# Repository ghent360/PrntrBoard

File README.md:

Prntr Board V1
======================
## *Deprecated*
**This project has run it's course. Most of the features are complete and there is little I can improve further. I have switched my focus to the [V2 design](https://github.com/ghent360/PrntrBoardV2).**

------------------

PrntrBoard is a 3D printer controller board designed to work with STM32 NUCLEO dev kits. The current version (V1) supports NUCLEO-64 series kits. The design is being developed on F446-RE kit, but other models could work as well. IMO the STM32F446 NUCLEO-64 kit offers very good performance (180MHz CPU) for the price ($15).

Some features of the board:
-----
  + 5x Trinamic super quiet drivers (TMC2130, TMC2660 or TMC2209)
  + Marlin 2.0 firmware
  + (2+2) controllable fans and 2x "always on" fan connectors
  + 3x min and max endstops for the x, y and z axis
  + 2x end stops for fillament end detection
  + SPI or I2C display connector for ST7735 or SSD1306 screen + one button and rotary encoder
  + Dual thermocouple connectors (for MAX31866, MAX31855 or MAX6675 boards)
  + Input voltage (Vin): 12-24V
  + selectable fan voltage (5V or Vin)

Because the NUCLEO-64 has limited number of IO pins, some compromises had to be made:
  + ~~No sd-card~~ (sd-card is added using new NUCLEO-64 compatible board)
  + The thermocouple connectors share pins with the E0 and E1 cool fan controls. You'll have to decide to use one or the other via jumpers on the board. Most printers I've seen come with "always on" extruder fans, the choice seemed like a worthy sacrifice.

Generic shortcuts I don't plan to improve:
------
  + ~~5V power supply is external. These are available from various resellers and fairly cheap - less than $1. No need to waste board layout space and component count.~~ (this has beed addresses with the new NUCLEO-64 compatible daugherboard)
  + Heated bed MOSFET - large heated beds consume a lot of power and it is challenging to provision the design for > 20A current (there is simply not enough copper space on the board to support this current). External heated bed MOSFETs are very affordable < $10 and support 20A-40A with no issues. If you have large heated bed - use external MOSFET or SSR.

Details
------
I use the daily build of KiCad (soon to be released V6) - let me know if you have trouble opening the files.

The current PCB desing is using 4 layer board, 6/6 mil track width/clearance, 12 mil min via hole size and 20 mil via diameter.

There are tree active branches:
  + tmc2130 - the board design for TMC2130 drivers
  + tmc2130-redesign - redesign of the TMC2130 branch with the nucleo board flipped
  + tmc2660 - the board design for TMC2660 drivers
  + tmc2209 - the board design for TMC2209 drivers

TMC2130 and TMC2660 PCB designs use the QFP version of the driver ICs, because they can handle a bit more power. The TMC2209 is available only in QFN package.

Status
------
TMC2130 version is table and been running for over a year. TMC2660 is being tested at the moment. Prototypes of the TMC2209 are being made.

old status:
I've been running a prototype of this board for a few months now and I'm very happy with the board stability. I'm trying to figure out how to make these at scale.

I have made prototypes of the TMC2130 board design (rev0) - the board has a few bugs, that are corrected in the rev1 version. Rev0 did not have LCD screen, it was added in Rev1. I'm trying to work-out the thermal design issues.
Rev1 board have been ordered and the dev branch is now switched to Rev2. The thermocouple connectors are added Rev2.
Rev2 borads have been ordered. The current working board is rev3. Added 2 more pins to the LCD connector
for the rotary encoder input. I also re-connected the E1 and E0 CS pins, so the LCD pins can be connected
to the hardware I2C pins. This way one can use SPI or I2C screens.

This branch is a redesign of the TMC2130 board. The main difference is that the NUCLEO board is flipped in a more natural position. In addition I'm now using a dedicated ground plane, larger heatsink areas for the mosfets. I'm much happier with the thermal layout of this branch.

The NUCLEO-64 board was limiting the design in many ways. I have a replacement board using STM32F407VE. This is 100 pin part. The new daughter board is the same form factor as the NUCLEO-64. It adds SPI EEPROM as well as native USB interface and micro SD-Card socket. The new board also has enough space for 24V to 5V buck converter, so power supply can beintegrated.

Tested circuits:
  + Heater control
  + Thermistor input
  + Fan control
  + Motor driver control
  + Z probe
  + End stops
  + Thermocuple interface (tested MAX31855 with Smoothieware)
  + LCD interface (tested REPRAP discount full graphics controller - the panel has issues
  sharing the SPI port with the TMC drivers. Could be solved with adapter board with extra AND gate)

Circuits that need verification:
  + Stall guard alert from the motor driver

Software
------

The software for the board is a clone of Marlin at [bugfix-2.0.x branch](https://github.com/ghent360/Marlin/tree/bugfix-2.0.x/ "Github.com") of my repository. It is quite usable. I keep it relatively in sync with the Marlin branch. *Note: there are other branches of Marlin, only the bugfix-2.0.x supports the STM32 microcontroller.*

Marlin is using Adruino IDE or Platform IO. I personally had issues with Platform IO not supporting the STM32F4 board, so I use Arduino version 1.8.5. To compile the firmware code you would need to install the [STM32 Arduino port](https://github.com/stm32duino/Arduino_Core_STM32 "www.stm32duino.com").

I'm also porting [Smoothieware](http://smoothieware.org) V1 to the board. So far I got the heater control and the stepper drivers working. My smoothie port is available [here](https://github.com/ghent360/Smoothieware-STM32F4 "Gitgub.com"). Please not the Smoothie port is not ready yet (there is an issue with the ADC). I have done only minimal tests so far.

Visit [my blog](https://blog.pcbxprt.com/) for status updates on the development of the board.

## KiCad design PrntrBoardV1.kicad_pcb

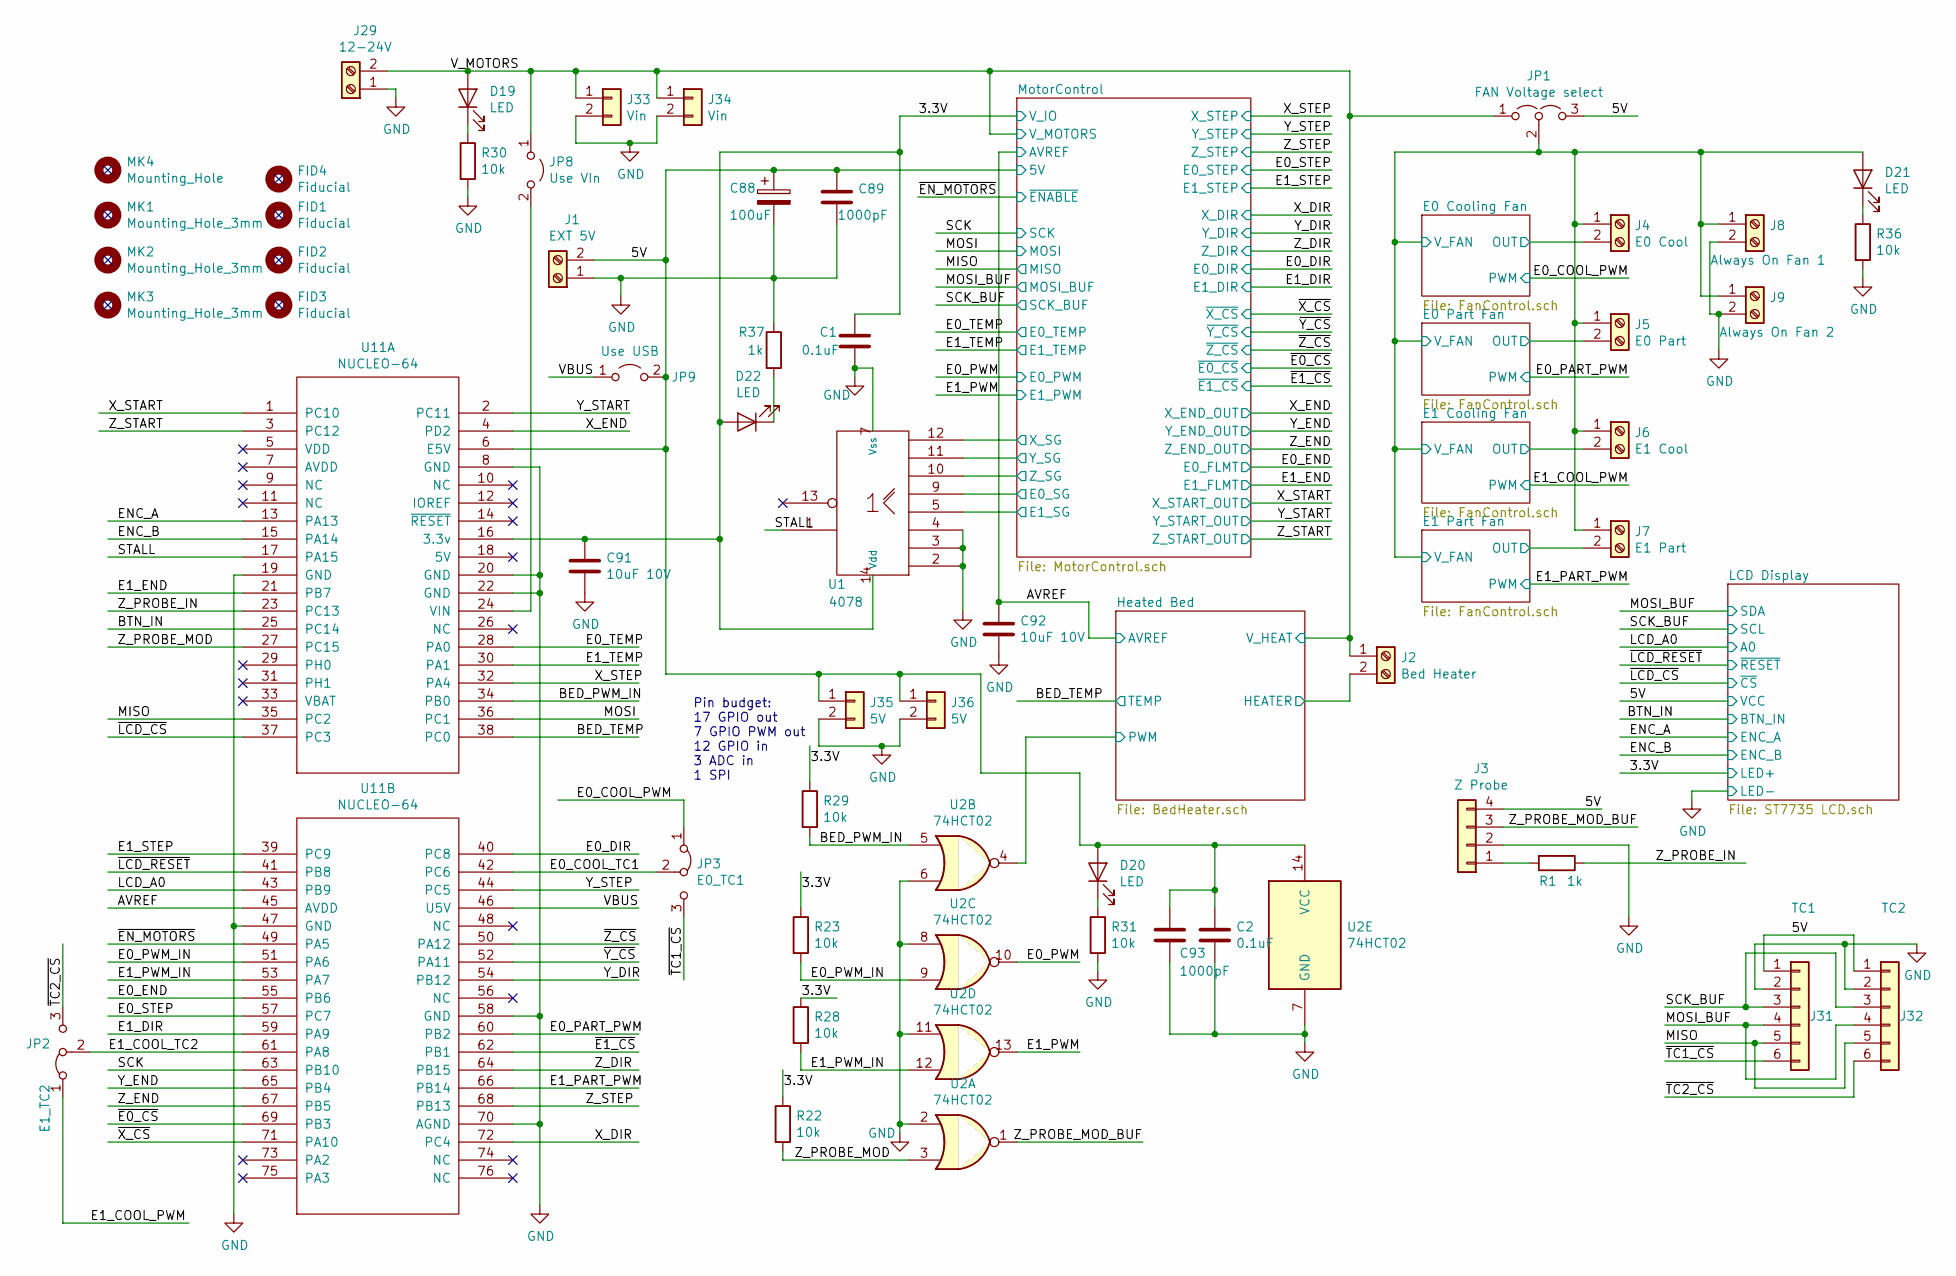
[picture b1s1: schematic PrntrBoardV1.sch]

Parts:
C1, C2: 0.1uF; C_0603_1608Metric
C88: 100uF; CP_Elec_6.3x7.7
C89, C93: 1000pF; C_0603_1608Metric
C91, C92: 10uF 10V; C_0603_1608Metric
D19, D20, D21, D22: LED; LED_0603_1608Metric
FID1, FID2, FID3, FID4: Fiducial; Fiducial_1mm_Dia_2.54mm_Outer_CopperTop
J1: EXT 5V; TerminalBlock_Phoenix_PT-1,5-2-3.5-H_1x02_P3.50mm_Horizontal
J2: Bed Heater; TerminalBlock_Phoenix_MKDS-1,5-2-5.08_1x02_P5.08mm_Horizont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
J3: Z Probe; PinHeader_1x04_P2.54mm_Vertical
J4: E0 Cool; TerminalBlock_Phoenix_PT-1,5-2-3.5-H_1x02_P3.50mm_Horizontal
J5: E0 Part; TerminalBlock_Phoenix_PT-1,5-2-3.5-H_1x02_P3.50mm_Horizontal
J6: E1 Cool; TerminalBlock_Phoenix_PT-1,5-2-3.5-H_1x02_P3.50mm_Horizontal
J7: E1 Part; TerminalBlock_Phoenix_PT-1,5-2-3.5-H_1x02_P3.50mm_Horizontal
J8: Always On Fan 1; TerminalBlock_Phoenix_PT-1,5-2-3.5-H_1x02_P3.50mm_Horizontal
J9: Always On Fan 2; TerminalBlock_Phoenix_PT-1,5-2-3.5-H_1x02_P3.50mm_Horizontal
J29: 12-24V; TerminalBlock_MetzConnect_Type701_RT11L02HGLU_1x02_P6.35mm_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
J31: TC1; PinHeader_1x06_P2.54mm_Vertical
J32: TC2; PinHeader_1x06_P2.54mm_Vertical
J33, J34: Vin; PinHeader_1x02_P2.54mm_Vertical
J35, J36: 5V; PinHeader_1x02_P2.54mm_Vertical
JP1: FAN Voltage select; PinHeader_1x03_P2.54mm_Vertical
JP2: E1_TC2; PinHeader_1x03_P2.54mm_Vertical
JP3: E0_TC1; PinHeader_1x03_P2.54mm_Vertical
JP8: Use VIn; PinHeader_1x02_P2.54mm_Vertical
JP9: Use USB; PinHeader_1x02_P2.54mm_Vertical
MK1, MK2, MK3: Mounting_Hole_3mm; MountingHole_3.2mm_M3
MK4: Mounting_Hole; MountingHole_3.2mm_M3
R1, R37: 1k; R_0603_1608Metric
R22, R23, R28, R29, R30, R31, R36: 10k; R_0603_1608Metric
U1: 4078; TSSOP-14_4.4x5mm_P0.65mm
U2: 74HCT02; TSSOP-14_4.4x5mm_P0.65mm
U11: NUCLEO-64; Nucleo-64

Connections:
/3.3V: C1.1, C91.1, D22.2 (A), R22.1, R23.1, R28.1, R29.1, U1.14 (Vdd), U11.16 (3.3v); also elsewhere on the board
/5V: C2.1, C88.1, C89.1, C93.1, D20.2 (A), J1.2, J3.4, J31.1, J32.1, J35.1, J36.1, JP1.3 (B), JP9.2 (B), U2.14 (VCC), U11.6 (E5V); also elsewhere on the board
/AVREF: C92.1, U11.45 (AVDD); also elsewhere on the board
/BED_PWM_IN: R29.2, U2.5, U11.34 (PB0)
/BED_TEMP: U11.38 (PC0); also elsewhere on the board
/BTN_IN: U11.25 (PC14); also elsewhere on the board
/E0_COOL_PWM: JP3.1 (A); also elsewhere on the board
/E0_COOL_TC1: JP3.2 (C), U11.42 (PC6)
/E0_DIR: U11.40 (PC8); also elsewhere on the board
/E0_END: U11.55 (PB6); also elsewhere on the board
/E0_PART_PWM: U11.60 (PB2); also elsewhere on the board
/E0_PWM: U2.10; also elsewhere on the board
/E0_PWM_IN: R23.2, U2.9, U11.51 (PA6)
/E0_SG: U1.9; also elsewhere on the board
/E0_STEP: U11.57 (PC7); also elsewhere on the board
/E0_TEMP: U11.28 (PA0); also elsewhere on the board
/E1_COOL_PWM: JP2.1 (A); also elsewhere on the board
/E1_COOL_TC2: JP2.2 (C), U11.61 (PA8)
/E1_DIR: U11.59 (PA9); also elsewhere on the board
/E1_END: U11.21 (PB7); also elsewhere on the board
/E1_PART_PWM: U11.66 (PB14); also elsewhere on the board
/E1_PWM: U2.13; also elsewhere on the board
/E1_PWM_IN: R28.2, U2.12, U11.53 (PA7)
/E1_SG: U1.5; also elsewhere on the board
/E1_STEP: U11.39 (PC9); also elsewhere on the board
/E1_TEMP: U11.30 (PA1); also elsewhere on the board
/ENC_A: U11.13 (PA13); also elsewhere on the board
/ENC_B: U11.15 (PA14); also elsewhere on the board
/LCD_A0: U11.43 (PB9); also elsewhere on the board
/MISO: J31.5, J32.5, U11.35 (PC2); also elsewhere on the board
/MOSI: U11.36 (PC1); also elsewhere on the board
/MOSI_BUF: J31.4, J32.4; also elsewhere on the board
/OUT: J4.2; also elsewhere on the board
/OUT_1: J7.2; also elsewhere on the board
/OUT_2: J5.2; also elsewhere on the board
/OUT_3: J6.2; also elsewhere on the board
/PWM: U2.4; also elsewhere on the board
/SCK: U11.63 (PB10); also elsewhere on the board
/SCK_BUF: J31.3, J32.3; also elsewhere on the board
/STALL: U1.1, U11.17 (PA15)
/VBUS: JP9.1 (A), U11.46 (U5V)
/V_FAN: D21.2 (A), J4.1, J5.1, J6.1, J7.1, J8.1, J9.1, JP1.2 (C); also elsewhere on the board
/V_MOTORS: D19.2 (A), J2.1, J29.2, J33.1, J34.1, JP1.1 (A), JP8.1 (A); also elsewhere on the board
/X_DIR: U11.72 (PC4); also elsewhere on the board
/X_END: U11.4 (PD2); also elsewhere on the board
/X_SG: U1.12; also elsewhere on the board
/X_START: U11.1 (PC10); also elsewhere on the board
/X_STEP: U11.32 (PA4); also elsewhere on the board
/Y_DIR: U11.54 (PB12); also elsewhere on the board
/Y_END: U11.65 (PB4); also elsewhere on the board
/Y_SG: U1.11; also elsewhere on the board
/Y_START: U11.2 (PC11); also elsewhere on the board
/Y_STEP: U11.44 (PC5); also elsewhere on the board
/Z_DIR: U11.64 (PB15); also elsewhere on the board
/Z_END: U11.67 (PB5); also elsewhere on the board
/Z_PROBE_IN: R1.1, U11.23 (PC13)
/Z_PROBE_MOD: R22.2, U2.3, U11.27 (PC15)
/Z_PROBE_MOD_BUF: J3.3, U2.1
/Z_SG: U1.10; also elsewhere on the board
/Z_START: U11.3 (PC12); also elsewhere on the board
/Z_STEP: U11.68 (PB13); also elsewhere on the board
/~E0_CS: U11.69 (PB3); also elsewhere on the board
/~E1_CS: U11.62 (PB1); also elsewhere on the board
/~EN_MOTORS: U11.49 (PA5); also elsewhere on the board
/~LCD_CS: U11.37 (PC3); also elsewhere on the board
/~LCD_RESET: U11.41 (PB8); also elsewhere on the board
/~TC1_CS: J31.6, JP3.3 (B)
/~TC2_CS: J32.6, JP2.3 (B)
/~X_CS: U11.71 (PA10); also elsewhere on the board
/~Y_CS: U11.52 (PA11); also elsewhere on the board
/~Z_CS: U11.50 (PA12); also elsewhere on the board
GND: C1.2, C2.2, C88.2, C89.2, C91.2, C92.2, C93.2, J1.1, J3.2, J8.2, J9.2, J29.1, J31.2, J32.2, J33.2, J34.2, J35.2, J36.2, R30.2, R31.2, R36.2, R37.1, U1.2, U1.3, U1.4, U1.7 (Vss), U2.2, U2.6, U2.7 (GND), U2.8, U2.11, U11.8 (GND), U11.19 (GND), U11.20 (GND), U11.22 (GND), U11.47 (GND), U11.58 (GND), U11.70 (AGND); also elsewhere on the board
unnamed: D19.1 (K), R30.1
unnamed: D20.1 (K), R31.1
unnamed: D21.1 (K), R36.1
unnamed: D22.1 (K), R37.2
unnamed: J3.1, R1.2
unnamed: JP8.2 (B), U11.24 (VIN)

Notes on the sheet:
Pin budget: 17 GPIO out 7 GPIO PWM out 12 GPIO in 3 ADC in 1 SPI

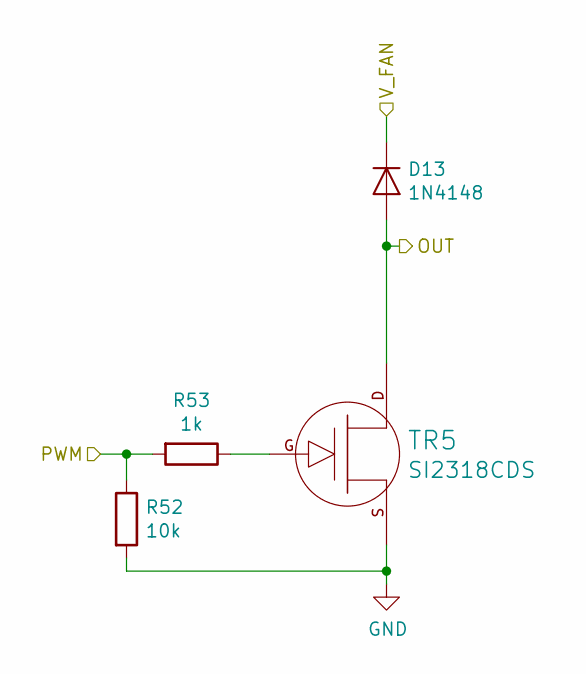
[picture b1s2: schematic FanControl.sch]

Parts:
D12: 1N4148; D_SOD-323_HandSoldering
R50: 10k; R_0603_1608Metric
R51: 1k; R_0603_1608Metric
TR4: SI2318CDS; SOT-23

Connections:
/E0_COOL_PWM: R50.1, R51.2; also elsewhere on the board
/OUT: D12.2 (A), TR4.D; also elsewhere on the board
/V_FAN: D12.1 (K); also elsewhere on the board
GND: R50.2, TR4.S; also elsewhere on the board
unnamed: R51.1, TR4.G

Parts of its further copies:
D13, D14, D15: 1N4148; D_SOD-323_HandSoldering
R52, R54, R56: 10k; R_0603_1608Metric
R53, R55, R57: 1k; R_0603_1608Metric
TR5, TR6, TR7: SI2318CDS; SOT-23

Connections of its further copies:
/E0_PART_PWM: R52.1, R53.2; also elsewhere on the board
/E1_COOL_PWM: R54.1, R55.2; also elsewhere on the board
/E1_PART_PWM: R56.1, R57.2; also elsewhere on the board
/OUT_1: D15.2 (A), TR7.D; also elsewhere on the board
/OUT_2: D13.2 (A), TR5.D; also elsewhere on the board
/OUT_3: D14.2 (A), TR6.D; also elsewhere on the board
/V_FAN: D13.1 (K), D14.1 (K), D15.1 (K); also elsewhere on the board
GND: R52.2, R54.2, R56.2, TR5.S, TR6.S, TR7.S; also elsewhere on the board
unnamed: R53.1, TR5.G
unnamed: R55.1, TR6.G
unnamed: R57.1, TR7.G

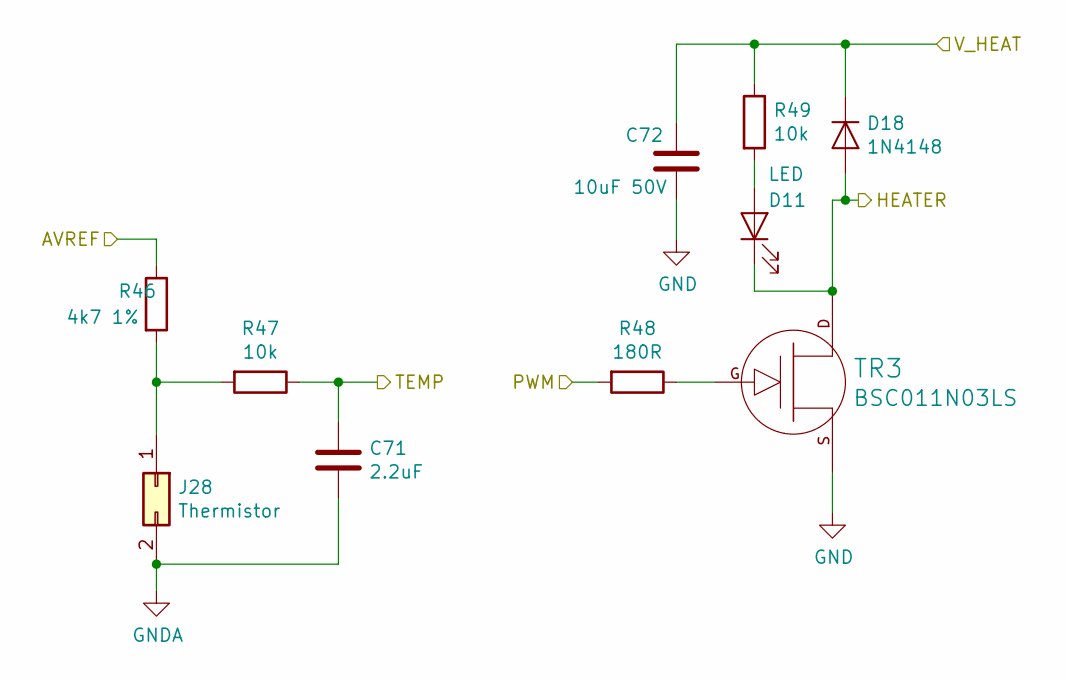
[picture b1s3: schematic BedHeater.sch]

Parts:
C16: 2.2uF; C_0603_1608Metric
C17: 10uF 50V; C_1206_3216Metric
D2: LED; LED_0603_1608Metric
D18: 1N4148; D_SOD-323_HandSoldering
J13: Thermistor; PinHeader_1x02_P2.54mm_Vertical
R8: 4k7 1%; R_0603_1608Metric
R9, R11: 10k; R_0603_1608Metric
R10: 180R; R_0603_1608Metric
TR1: BSC011N03LS; PG-TDSON-8-FL

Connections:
/AVREF: R8.1; also elsewhere on the board
/E0_PWM: R10.2; also elsewhere on the board
/E0_TEMP: C16.1, R9.1; also elsewhere on the board
/V_MOTORS: C17.1, D18.1 (K), R11.1; also elsewhere on the board
GND: C16.2, C17.2, J13.2, TR1.S; also elsewhere on the board
unnamed: D2.2 (A), R11.2
unnamed: J13.1, R8.2, R9.2
unnamed: R10.1, TR1.G

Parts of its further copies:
C69, C71: 2.2uF; C_0603_1608Metric
C70, C72: 10uF 50V; C_1206_3216Metric
D10, D11: LED; LED_0603_1608Metric
J27, J28: Thermistor; PinHeader_1x02_P2.54mm_Vertical
R42, R46: 4k7 1%; R_0603_1608Metric
R43, R45, R47, R49: 10k; R_0603_1608Metric
R44, R48: 180R; R_0603_1608Metric
TR3: BSC011N03LS; PG-TDSON-8-FL

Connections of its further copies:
/AVREF: R42.1, R46.1; also elsewhere on the board
/BED_TEMP: C71.1, R47.1; also elsewhere on the board
/E1_PWM: R44.2; also elsewhere on the board
/E1_TEMP: C69.1, R43.1; also elsewhere on the board
/PWM: R48.2; also elsewhere on the board
/V_MOTORS: C70.1, C72.1, R45.1, R49.1; also elsewhere on the board
GND: C69.2, C70.2, C71.2, C72.2, J27.2, J28.2, TR3.S; also elsewhere on the board
unnamed: D10.2 (A), R45.2
unnamed: D11.2 (A), R49.2
unnamed: J27.1, R42.2, R43.2
unnamed: J28.1, R46.2, R47.2
unnamed 145: R44.1; also elsewhere on the board
unnamed: R48.1, TR3.G

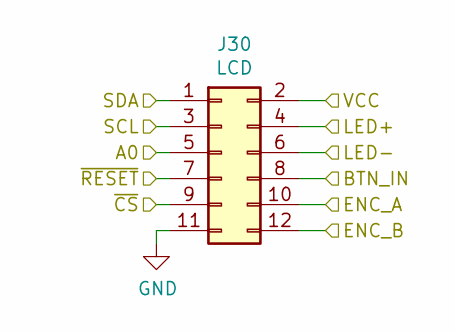
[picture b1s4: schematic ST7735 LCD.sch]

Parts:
J30: LCD; IDC-Header_2x06_P2.54mm_Vertical

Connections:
/3.3V: J30.4; also elsewhere on the board
/5V: J30.2; also elsewhere on the board
/BTN_IN: J30.8; also elsewhere on the board
/ENC_A: J30.10; also elsewhere on the board
/ENC_B: J30.12; also elsewhere on the board
/LCD_A0: J30.5; also elsewhere on the board
/MOSI_BUF: J30.1; also elsewhere on the board
/SCK_BUF: J30.3; also elsewhere on the board
/~LCD_CS: J30.9; also elsewhere on the board
/~LCD_RESET: J30.7; also elsewhere on the board
GND: J30.6, J30.11; also elsewhere on the board

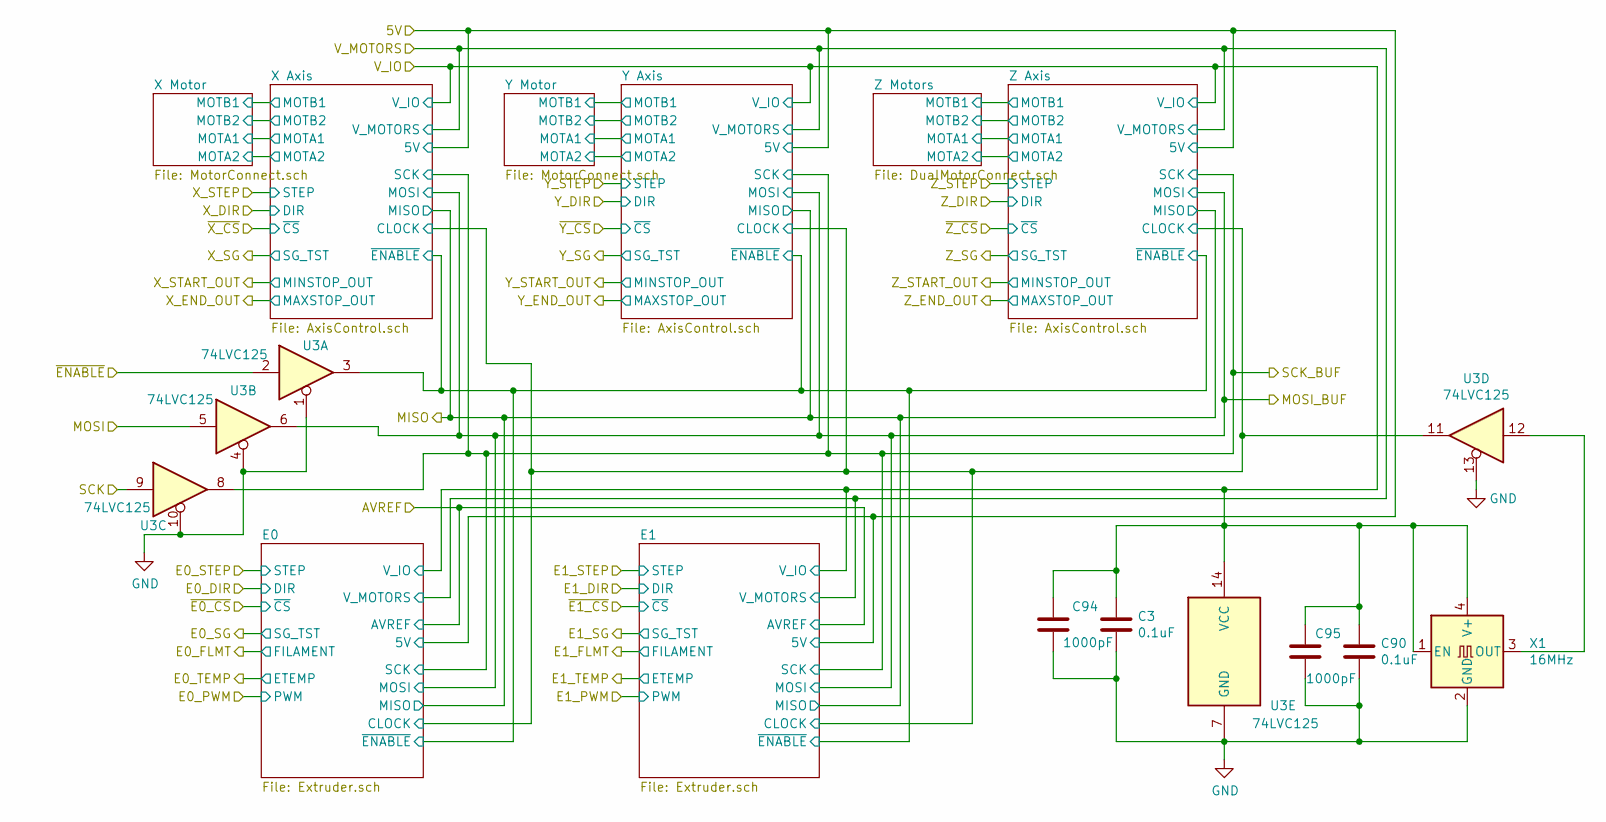
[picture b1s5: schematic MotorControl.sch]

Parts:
C3, C90: 0.1uF; C_0603_1608Metric
C94, C95: 1000pF; C_0603_1608Metric
U3: 74LVC125; TSSOP-14_4.4x5mm_P0.65mm
X1: 16MHz; Oscillator_SMD_EuroQuartz_XO32-4Pin_3.2x2.5mm_HandSoldering

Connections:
/3.3V: C3.1, C90.1, C94.1, C95.1, U3.14 (VCC), X1.1 (EN), X1.4 (V+); also elsewhere on the board
/MOSI: U3.5; also elsewhere on the board
/MOSI_BUF: U3.6; also elsewhere on the board
/MotorControl/CLOCK: U3.11; also elsewhere on the board
/MotorControl/~ENABLE_1: U3.3; also elsewhere on the board
/SCK: U3.9; also elsewhere on the board
/SCK_BUF: U3.8; also elsewhere on the board
/~EN_MOTORS: U3.2; also elsewhere on the board
GND: C3.2, C90.2, C94.2, C95.2, U3.1, U3.4, U3.7 (GND), U3.10, U3.13, X1.2 (GND); also elsewhere on the board
unnamed: U3.12, X1.3 (OUT)

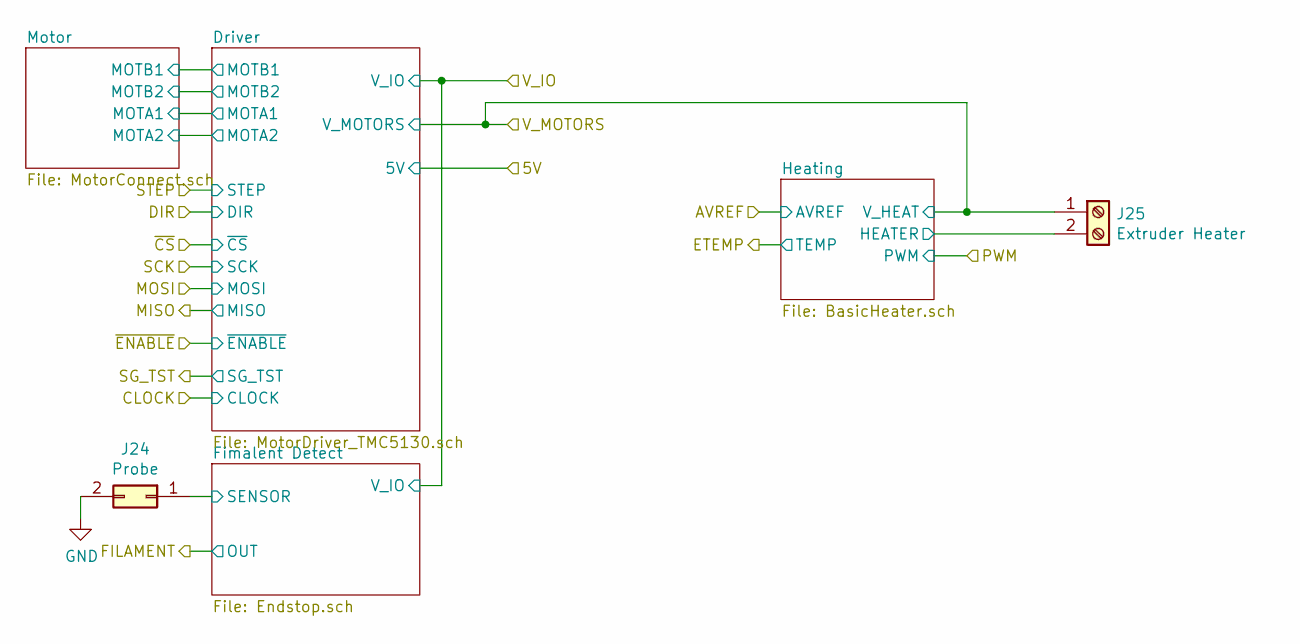
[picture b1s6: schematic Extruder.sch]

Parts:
J10: Probe; PinHeader_1x02_P2.54mm_Vertical
J11: Extruder Heater; TerminalBlock_Phoenix_PT-1,5-2-3.5-H_1x02_P3.50mm_Horizontal

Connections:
/MotorControl/E0/SENSOR: J10.1; also elsewhere on the board
/V_MOTORS: J11.1; also elsewhere on the board
GND: J10.2; also elsewhere on the board

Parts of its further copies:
J24: Probe; PinHeader_1x02_P2.54mm_Vertical
J25: Extruder Heater; TerminalBlock_Phoenix_PT-1,5-2-3.5-H_1x02_P3.50mm_Horizontal

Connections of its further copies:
/MotorControl/E1/SENSOR: J24.1; also elsewhere on the board
/V_MOTORS: J25.1; also elsewhere on the board
GND: J24.2; also elsewhere on the board

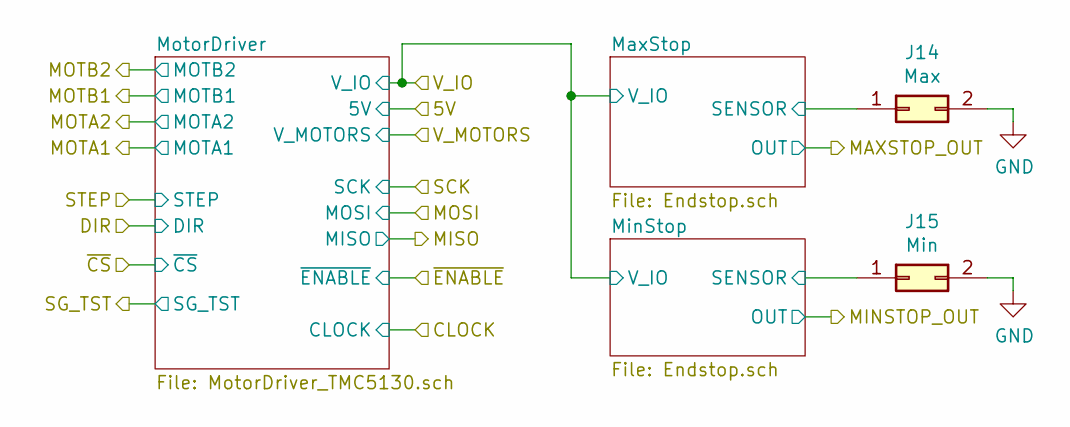
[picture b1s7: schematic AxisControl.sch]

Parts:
J14: Max; PinHeader_1x02_P2.54mm_Vertical
J15: Min; PinHeader_1x02_P2.54mm_Vertical

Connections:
/MotorControl/X Axis/SENSOR: J14.1; also elsewhere on the board
/MotorControl/X Axis/SENSOR_1: J15.1; also elsewhere on the board
GND: J14.2, J15.2; also elsewhere on the board

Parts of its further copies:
J16, J18: Max; PinHeader_1x02_P2.54mm_Vertical
J17, J19: Min; PinHeader_1x02_P2.54mm_Vertical

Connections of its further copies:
/MotorControl/Y Axis/SENSOR: J16.1; also elsewhere on the board
/MotorControl/Y Axis/SENSOR_1: J17.1; also elsewhere on the board
/MotorControl/Z Axis/SENSOR: J18.1; also elsewhere on the board
/MotorControl/Z Axis/SENSOR_1: J19.1; also elsewhere on the board
GND: J16.2, J17.2, J18.2, J19.2; also elsewhere on the board

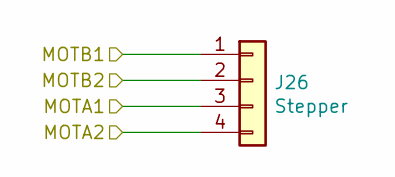
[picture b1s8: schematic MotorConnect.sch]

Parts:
J12: Stepper; PinHeader_1x04_P2.54mm_Vertical

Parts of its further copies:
J20, J21, J22, J23, J26: Stepper; PinHeader_1x04_P2.54mm_Vertical

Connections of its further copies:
/MotorControl/MOTA1: J20.3; also elsewhere on the board
/MotorControl/MOTA1_1: J23.3; also elsewhere on the board
/MotorControl/MOTA1_2: J21.3; also elsewhere on the board
/MotorControl/MOTA2: J20.4; also elsewhere on the board
/MotorControl/MOTA2_1: J22.4; also elsewhere on the board
/MotorControl/MOTA2_2: J21.4; also elsewhere on the board
/MotorControl/MOTB1: J20.1; also elsewhere on the board
/MotorControl/MOTB1_1: J23.1; also elsewhere on the board
/MotorControl/MOTB1_2: J21.1; also elsewhere on the board
/MotorControl/MOTB2: J20.2; also elsewhere on the board
/MotorControl/MOTB2_1: J22.2; also elsewhere on the board
/MotorControl/MOTB2_2: J21.2; also elsewhere on the board
/MotorControl/Z Motors/MOTA1_1: J22.3, J23.4
/MotorControl/Z Motors/MOTB2_1: J22.1, J23.2

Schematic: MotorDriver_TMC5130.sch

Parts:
C4, C74: 10uF 50V; C_1206_3216Metric
C5: 100uF 35V; CP_Elec_6.3x7.7
C6, C86, C87: 0.1uF 50V; C_0402_1005Metric
C7: 0.47uF; C_0603_1608Metric
C8, C85: 0.1uF; C_0603_1608Metric
C10, C11, C12, C13: 1000pF; C_0603_1608Metric
C84: 0.022uF 50V; C_0603_1608Metric
R20, R21: 0R15 0.5W; R_1206_3216Metric
U8: TMC5130; tmc5130-nc

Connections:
/3.3V: C8.1, U8.10 (VCC_IO); also elsewhere on the board
/5V: C7.2, U8.34 (VCC); also elsewhere on the board
/E1_DIR: U8.9 (DIR); also elsewhere on the board
/E1_SG: U8.27 (DIAG1); also elsewhere on the board
/E1_STEP: U8.8 (STEP); also elsewhere on the board
/MISO: U8.7 (SDO); also elsewhere on the board
/MOSI_BUF: U8.5 (SDI); also elsewhere on the board
/MotorControl/CLOCK: U8.2 (CLK); also elsewhere on the board
/MotorControl/~ENABLE_1: U8.29 (~ENABLE); also elsewhere on the board
/SCK_BUF: U8.4 (SCK); also elsewhere on the board
/V_MOTORS: C4.1, C5.1, C6.1, C74.1, U8.21 (VS), U8.39 (VSA), U8.40 (VS); also elsewhere on the board
/~E1_CS: U8.3 (~CS); also elsewhere on the board
GND: C4.2, C5.2, C7.1, C8.2, C10.1, C11.1, C12.1, C13.1, C74.2, C85.1, C86.2, C87.2, R20.2, R21.2, U8.1 (TST_MODE), U8.6 (N/C), U8.13 (GNDP), U8.24 (ENDB_DCEN), U8.31 (N/C), U8.32 (GNDA), U8.36 (N/C), U8.48 (GNDP), U8.49 (PAD); also elsewhere on the board
unnamed: C84.1, U8.37 (CPI)
unnamed: C84.2, U8.35 (CPO)
unnamed: C85.2, U8.33 (5VOUT)
unnamed: C86.1, R20.1, U8.17 (BRB)
unnamed: C87.1, R21.1, U8.44 (BRA)

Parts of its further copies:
C9, C36, C62, C80: 0.022uF 50V; C_0603_1608Metric
C14, C22, C35, C41, C48, C61, C67, C81: 0.1uF; C_0603_1608Metric
C18, C31, C44, C57, C73, C75, C76, C77: 10uF 50V; C_1206_3216Metric
C19, C32, C45, C58: 100uF 35V; CP_Elec_6.3x7.7
C20, C23, C28, C33, C46, C49, C54, C59, C78, C79, C82, C83: 0.1uF 50V; C_0402_1005Metric
C21, C34, C47, C60: 0.47uF; C_0603_1608Metric
C24, C25, C26, C27, C37, C38, C39, C40, C50, C51, C52, C53, C63, C64, C65, C66: 1000pF; C_0603_1608Metric
R2, R3, R4, R5, R12, R13, R14, R15: 0R15 0.5W; R_1206_3216Metric
U4, U5, U6, U7: TMC5130; tmc5130-nc

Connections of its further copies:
/3.3V: C22.1, C35.1, C48.1, C61.1, U4.10 (VCC_IO), U5.10 (VCC_IO), U6.10 (VCC_IO), U7.10 (VCC_IO); also elsewhere on the board
/5V: C21.2, C34.2, C47.2, C60.2, U4.34 (VCC), U5.34 (VCC), U6.34 (VCC), U7.34 (VCC); also elsewhere on the board
/E0_DIR: U4.9 (DIR); also elsewhere on the board
/E0_SG: U4.27 (DIAG1); also elsewhere on the board
/E0_STEP: U4.8 (STEP); also elsewhere on the board
/MISO: U4.7 (SDO), U5.7 (SDO), U6.7 (SDO), U7.7 (SDO); also elsewhere on the board
/MOSI_BUF: U4.5 (SDI), U5.5 (SDI), U6.5 (SDI), U7.5 (SDI); also elsewhere on the board
/MotorControl/CLOCK: U4.2 (CLK), U5.2 (CLK), U6.2 (CLK), U7.2 (CLK); also elsewhere on the board
/MotorControl/MOTA1: C25.2, U5.46 (OA1); also elsewhere on the board
/MotorControl/MOTA1_1: C51.2, U7.46 (OA1); also elsewhere on the board
/MotorControl/MOTA1_2: C38.2, U6.46 (OA1); also elsewhere on the board
/MotorControl/MOTA2: C26.2, U5.42 (OA2); also elsewhere on the board
/MotorControl/MOTA2_1: C52.2, U7.42 (OA2); also elsewhere on the board
/MotorControl/MOTA2_2: C39.2, U6.42 (OA2); also elsewhere on the board
/MotorControl/MOTB1: C24.2, U5.15 (OB1); also elsewhere on the board
/MotorControl/MOTB1_1: C50.2, U7.15 (OB1); also elsewhere on the board
/MotorControl/MOTB1_2: C37.2, U6.15 (OB1); also elsewhere on the board
/MotorControl/MOTB2: C27.2, U5.19 (OB2); also elsewhere on the board
/MotorControl/MOTB2_1: C53.2, U7.19 (OB2); also elsewhere on the board
/MotorControl/MOTB2_2: C40.2, U6.19 (OB2); also elsewhere on the board
/MotorControl/~ENABLE_1: U4.29 (~ENABLE), U5.29 (~ENABLE), U6.29 (~ENABLE), U7.29 (~ENABLE); also elsewhere on the board
/SCK_BUF: U4.4 (SCK), U5.4 (SCK), U6.4 (SCK), U7.4 (SCK); also elsewhere on the board
/V_MOTORS: C18.1, C19.1, C20.1, C31.1, C32.1, C33.1, C44.1, C45.1, C46.1, C57.1, C58.1, C59.1, C73.1, C75.1, C76.1, C77.1, U4.21 (VS), U4.39 (VSA), U4.40 (VS), U5.21 (VS), U5.39 (VSA), U5.40 (VS), U6.21 (VS), U6.39 (VSA), U6.40 (VS), U7.21 (VS), U7.39 (VSA), U7.40 (VS); also elsewhere on the board
/X_DIR: U5.9 (DIR); also elsewhere on the board
/X_SG: U5.27 (DIAG1); also elsewhere on the board
/X_STEP: U5.8 (STEP); also elsewhere on the board
/Y_DIR: U6.9 (DIR); also elsewhere on the board
/Y_SG: U6.27 (DIAG1); also elsewhere on the board
/Y_STEP: U6.8 (STEP); also elsewhere on the board
/Z_DIR: U7.9 (DIR); also elsewhere on the board
/Z_SG: U7.27 (DIAG1); also elsewhere on the board
/Z_STEP: U7.8 (STEP); also elsewhere on the board
/~E0_CS: U4.3 (~CS); also elsewhere on the board
/~X_CS: U5.3 (~CS); also elsewhere on the board
/~Y_CS: U6.3 (~CS); also elsewhere on the board
/~Z_CS: U7.3 (~CS); also elsewhere on the board
GND: C14.1, C18.2, C19.2, C21.1, C22.2, C23.2, C24.1, C25.1, C26.1, C27.1, C28.2, C31.2, C32.2, C34.1, C35.2, C37.1, C38.1, C39.1, C40.1, C41.1, C44.2, C45.2, C47.1, C48.2, C49.2, C50.1, C51.1, C52.1, C53.1, C54.2, C57.2, C58.2, C60.1, C61.2, C63.1, C64.1, C65.1, C66.1, C67.1, C73.2, C75.2, C76.2, C77.2, C78.2, C79.2, C81.1, C82.2, C83.2, R2.2, R3.2, R4.2, R5.2, R12.2, R13.2, R14.2, R15.2, U4.1 (TST_MODE), U4.6 (N/C), U4.13 (GNDP), U4.24 (ENDB_DCEN), U4.31 (N/C), U4.32 (GNDA), U4.36 (N/C), U4.48 (GNDP), U4.49 (PAD), U5.1 (TST_MODE), U5.6 (N/C), U5.13 (GNDP), U5.24 (ENDB_DCEN), U5.31 (N/C), U5.32 (GNDA), U5.36 (N/C), U5.48 (GNDP), U5.49 (PAD), U6.1 (TST_MODE), U6.6 (N/C), U6.13 (GNDP), U6.24 (ENDB_DCEN), U6.31 (N/C), U6.32 (GNDA), U6.36 (N/C), U6.48 (GNDP), U6.49 (PAD), U7.1 (TST_MODE), U7.6 (N/C), U7.13 (GNDP), U7.24 (ENDB_DCEN), U7.31 (N/C), U7.32 (GNDA), U7.36 (N/C), U7.48 (GNDP), U7.49 (PAD); also elsewhere on the board
unnamed: C9.1, U4.37 (CPI)
unnamed: C9.2, U4.35 (CPO)
unnamed: C14.2, U4.33 (5VOUT)
unnamed: C20.2, U5.38 (VCP)
unnamed: C23.1, R2.1, U4.17 (BRB)
unnamed: C28.1, R3.1, U4.44 (BRA)
unnamed: C33.2, U6.38 (VCP)
unnamed: C36.1, U5.37 (CPI)
unnamed: C36.2, U5.35 (CPO)
unnamed: C41.2, U5.33 (5VOUT)
unnamed: C46.2, U7.38 (VCP)
unnamed: C49.1, R4.1, U5.17 (BRB)
unnamed: C54.1, R5.1, U5.44 (BRA)
unnamed: C62.1, U6.37 (CPI)
unnamed: C62.2, U6.35 (CPO)
unnamed: C67.2, U6.33 (5VOUT)
unnamed: C78.1, R12.1, U6.17 (BRB)
unnamed: C79.1, R13.1, U6.44 (BRA)
unnamed: C80.1, U7.37 (CPI)
unnamed: C80.2, U7.35 (CPO)
unnamed: C81.2, U7.33 (5VOUT)
unnamed: C82.1, R14.1, U7.17 (BRB)
unnamed: C83.1, R15.1, U7.44 (BRA)

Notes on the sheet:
1000pf capacitors min 50V rating

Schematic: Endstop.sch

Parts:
C15: 1000pF; C_0603_1608Metric
D1: LED; LED_0603_1608Metric
R6: 10k; R_0603_1608Metric
R7: 1k; R_0603_1608Metric

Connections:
/3.3V: R7.1; also elsewhere on the board
/E0_END: R6.1; also elsewhere on the board
/MotorControl/E0/SENSOR: C15.1, D1.1 (K), R6.2; also elsewhere on the board
GND: C15.2; also elsewhere on the board
unnamed: D1.2 (A), R7.2

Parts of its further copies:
C29, C30, C42, C43, C55, C56, C68: 1000pF; C_0603_1608Metric
D3, D4, D5, D6, D7, D8, D9: LED; LED_0603_1608Metric
R16, R18, R24, R26, R32, R34, R40: 10k; R_0603_1608Metric
R17, R19, R25, R27, R33, R35, R41: 1k; R_0603_1608Metric

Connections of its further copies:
/3.3V: R17.1, R19.1, R25.1, R27.1, R33.1, R35.1, R41.1; also elsewhere on the board
/E1_END: R40.1; also elsewhere on the board
/MotorControl/E1/SENSOR: C68.1, D9.1 (K), R40.2; also elsewhere on the board
/MotorControl/X Axis/SENSOR: C29.1, D3.1 (K), R16.2; also elsewhere on the board
/MotorControl/X Axis/SENSOR_1: C30.1, D4.1 (K), R18.2; also elsewhere on the board
/MotorControl/Y Axis/SENSOR: C42.1, D5.1 (K), R24.2; also elsewhere on the board
/MotorControl/Y Axis/SENSOR_1: C43.1, D6.1 (K), R26.2; also elsewhere on the board
/MotorControl/Z Axis/SENSOR: C55.1, D7.1 (K), R32.2; also elsewhere on the board
/MotorControl/Z Axis/SENSOR_1: C56.1, D8.1 (K), R34.2; also elsewhere on the board
/X_END: R16.1; also elsewhere on the board
/X_START: R18.1; also elsewhere on the board
/Y_END: R24.1; also elsewhere on the board
/Y_START: R26.1; also elsewhere on the board
/Z_END: R32.1; also elsewhere on the board
/Z_START: R34.1; also elsewhere on the board
GND: C29.2, C30.2, C42.2, C43.2, C55.2, C56.2, C68.2; also elsewhere on the board
unnamed: D3.2 (A), R17.2
unnamed: D4.2 (A), R19.2
unnamed: D5.2 (A), R25.2
unnamed: D6.2 (A), R27.2
unnamed: D7.2 (A), R33.2
unnamed: D8.2 (A), R35.2
unnamed: D9.2 (A), R41.2

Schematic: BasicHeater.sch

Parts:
C16: 2.2uF; C_0603_1608Metric
C17: 10uF 50V; C_1206_3216Metric
D2: LED; LED_0603_1608Metric
D17: 1N4148; D_SOD-323_HandSoldering
J13: Thermistor; PinHeader_1x02_P2.54mm_Vertical
R8: 4k7 1%; R_0603_1608Metric
R9, R11: 10k; R_0603_1608Metric
R10: 180R; R_0603_1608Metric
TR1: PSMN7R0-30YL; SOT-669_LFPAK

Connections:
/AVREF: R8.1; also elsewhere on the board
/E0_PWM: R10.2; also elsewhere on the board
/E0_TEMP: C16.1, R9.1; also elsewhere on the board
/V_MOTORS: C17.1, D17.1 (K), R11.1; also elsewhere on the board
GND: C16.2, C17.2, J13.2, TR1.S; also elsewhere on the board
unnamed: D2.2 (A), R11.2
unnamed: J13.1, R8.2, R9.2
unnamed: R10.1, TR1.G

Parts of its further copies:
C69, C71: 2.2uF; C_0603_1608Metric
C70, C72: 10uF 50V; C_1206_3216Metric
D10, D11: LED; LED_0603_1608Metric
D16: 1N4148; D_SOD-323_HandSoldering
J27, J28: Thermistor; PinHeader_1x02_P2.54mm_Vertical
R42, R46: 4k7 1%; R_0603_1608Metric
R43, R45, R47, R49: 10k; R_0603_1608Metric
R44, R48: 180R; R_0603_1608Metric
TR2: PSMN7R0-30YL; SOT-669_LFPAK

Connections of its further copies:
/AVREF: R42.1, R46.1; also elsewhere on the board
/BED_TEMP: C71.1, R47.1; also elsewhere on the board
/E1_PWM: R44.2; also elsewhere on the board
/E1_TEMP: C69.1, R43.1; also elsewhere on the board
/PWM: R48.2; also elsewhere on the board
/V_MOTORS: C70.1, C72.1, D16.1 (K), R45.1, R49.1; also elsewhere on the board
GND: C69.2, C70.2, C71.2, C72.2, J27.2, J28.2, TR2.S; also elsewhere on the board
unnamed: D10.2 (A), R45.2
unnamed: D11.2 (A), R49.2
unnamed: J27.1, R42.2, R43.2
unnamed: J28.1, R46.2, R47.2
unnamed: R44.1, TR2.G
unnamed 146: R48.1; also elsewhere on the board

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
